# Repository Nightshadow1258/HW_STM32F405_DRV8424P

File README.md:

# STM32F405_DRV8424P
This project contains all files for a Stepper/2xDC-Motor Controller based on a STM32F405 MCU and a DRV8424P GDU.

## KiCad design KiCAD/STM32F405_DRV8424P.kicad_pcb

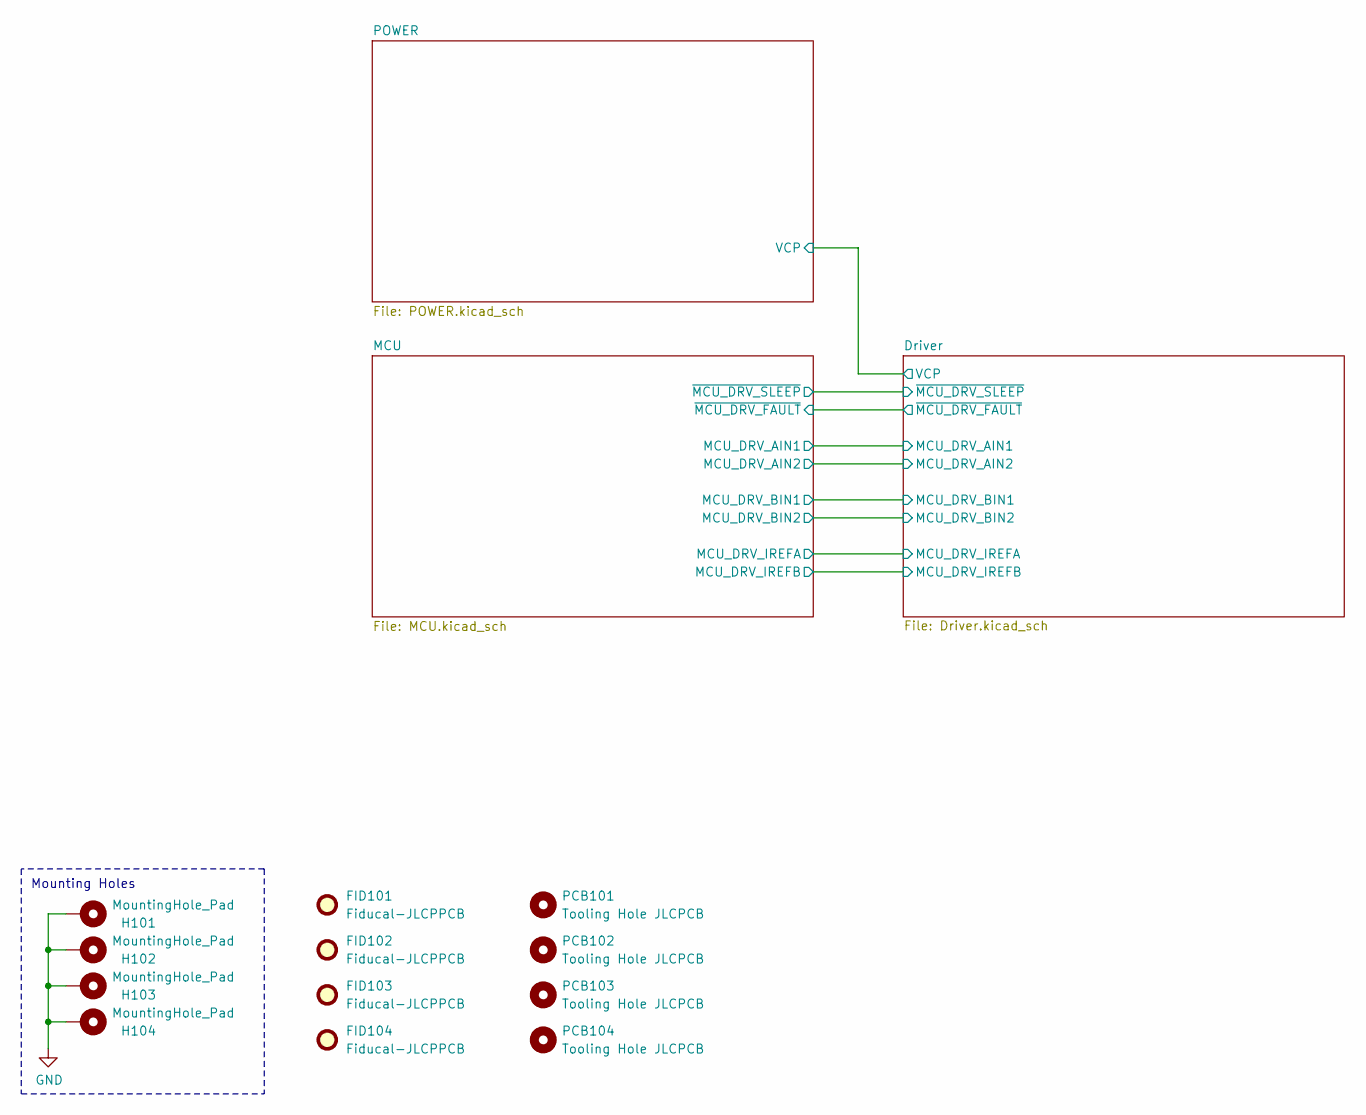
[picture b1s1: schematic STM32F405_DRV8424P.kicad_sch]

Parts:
FID101, FID102, FID103, FID104: Fiducal-JLCPPCB; PCB-FID-JLCPCB
H101, H102, H103, H104: MountingHole_Pad; MountingHole_4.3mm_M4_Pad_Via
PCB101, PCB102, PCB103, PCB104: Tooling Hole JLCPCB; PCB-NPTH-JLCPCB

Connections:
GND: H101.1, H102.1, H103.1, H104.1; also elsewhere on the board

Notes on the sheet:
Mounting Holes

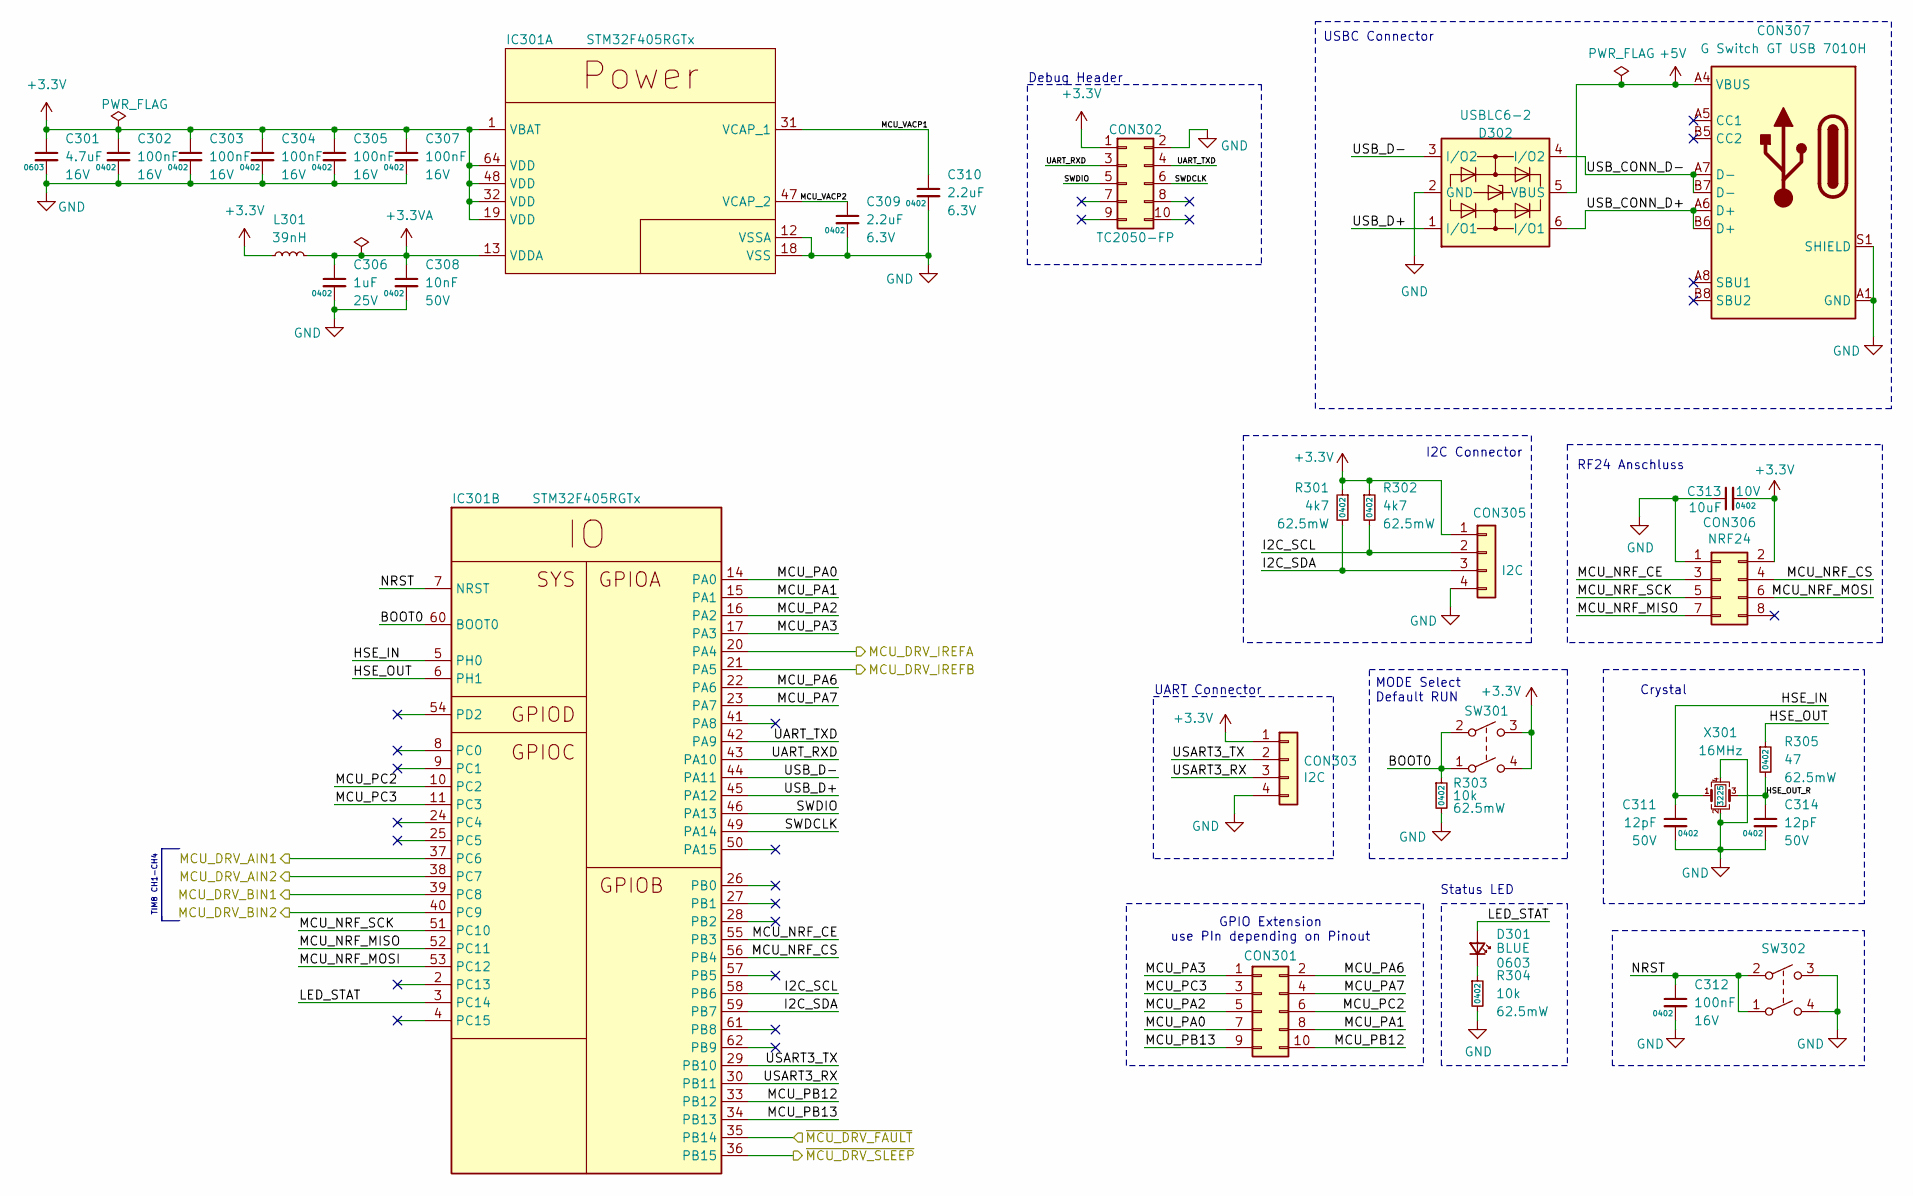
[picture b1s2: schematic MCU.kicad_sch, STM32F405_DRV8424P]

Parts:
C301: 4.7uF; C_0603_1608Metric; Voltage 16V; LCSC Part # C19666
C302, C303, C304, C305, C307, C312: 100nF; C_0402_1005Metric; Voltage 16V; LCSC Part # C1525
C306: 1uF; C_0402_1005Metric; Voltage 25V; LCSC Part # C52923
C308: 10nF; C_0402_1005Metric; Voltage 50V; LCSC Part # C15195
C309, C310: 2.2uF; C_0402_1005Metric; Voltage 6.3V; LCSC Part # C12530
C311, C314: 12pF; C_0402_1005Metric; Voltage 50V; LCSC Part # C1547
C313: 10uF; C_0603_1608Metric; Voltage 10V; LCSC Part # C96446
CON301: GPIO; PinHeader_2x05_P2.54mm_Vertical
CON302: TC2050-FP; CON-TAG-CONNECT_TC2050-IDC
CON303, CON305: I2C; PinHeader_1x04_P2.54mm_Vertical
CON306: NRF24; PinHeader_2x04_P2.54mm_Vertical
CON307: G Switch GT USB 7010H; CON-GEN-USB_C-16P; LCSC Part # C2988369
D301: BLUE; D_0603_1608Metric; LCSC Part # C965807
D302: USBLC6-2; SOT-23-6; LCSC Part # C7519
IC301: STM32F405RGTx; LQFP-64_10x10mm_P0.5mm; LCSC Part # C15742
L301: 39nH; L_0402_1005Metric; LCSC Part # C26443
R301, R302: 4k7; R_0402_1005Metric; Power Rating 62.5mW; LCSC Part # C25900
R303, R304: 10k; R_0402_1005Metric; Power Rating 62.5mW; LCSC Part # C25744
R305: 47; R_0402_1005Metric; Power Rating 62.5mW; LCSC Part # C25118
SW301, SW302: SW-GEN-TS-1187A; SW-PUSH-DPST-XKS-TS-1187A; LCSC Part # C318884
X301: 16MHz; Crystal_SMD_3225-4Pin_3.2x2.5mm; LCSC Part # C12668

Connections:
+3.3V: C301.1, C302.1, C303.1, C304.1, C305.1, C307.1, C313.2, CON302.1, CON303.1, CON305.1, CON306.2, IC301.1 (VBAT), IC301.19 (VDD), IC301.32 (VDD), IC301.48 (VDD), IC301.64 (VDD), L301.1, R301.1, R302.1, SW301.3 (4), SW301.4; also elsewhere on the board
+3.3VA: C306.1, C308.1, IC301.13 (VDDA), L301.2
+5V: CON307.A4 (VBUS), CON307.A9 (VBUS), CON307.B4 (VBUS), CON307.B9 (VBUS), D302.5 (VBUS); also elsewhere on the board
/Driver/MCU_DRV_AIN1: IC301.37 (PC6); also elsewhere on the board
/Driver/MCU_DRV_AIN2: IC301.38 (PC7); also elsewhere on the board
/Driver/MCU_DRV_BIN1: IC301.39 (PC8); also elsewhere on the board
/Driver/MCU_DRV_BIN2: IC301.40 (PC9); also elsewhere on the board
/Driver/MCU_DRV_IREFA: IC301.20 (PA4); also elsewhere on the board
/Driver/MCU_DRV_IREFB: IC301.21 (PA5); also elsewhere on the board
/Driver/~MCU_DRV_FAULT: IC301.35 (PB14); also elsewhere on the board
/Driver/~MCU_DRV_SLEEP: IC301.36 (PB15); also elsewhere on the board
/MCU/BOOT0: IC301.60 (BOOT0), R303.1, SW301.1, SW301.2 (3)
/MCU/HSE_IN: C311.1, IC301.5 (PH0), X301.1
/MCU/HSE_OUT: IC301.6 (PH1), R305.1
/MCU/HSE_OUT_R: C314.1, R305.2, X301.3
/MCU/I2C_SCL: CON305.2, IC301.58 (PB6), R302.2
/MCU/I2C_SDA: CON305.3, IC301.59 (PB7), R301.2
/MCU/LED_STAT: D301.2 (A), IC301.3 (PC14)
/MCU/MCU_NRF_CE: CON306.3, IC301.55 (PB3)
/MCU/MCU_NRF_CS: CON306.4, IC301.56 (PB4)
/MCU/MCU_NRF_MISO: CON306.7, IC301.52 (PC11)
/MCU/MCU_NRF_MOSI: CON306.6, IC301.53 (PC12)
/MCU/MCU_NRF_SCK: CON306.5, IC301.51 (PC10)
/MCU/MCU_PA0: CON301.7, IC301.14 (PA0)
/MCU/MCU_PA1: CON301.8, IC301.15 (PA1)
/MCU/MCU_PA2: CON301.5, IC301.16 (PA2)
/MCU/MCU_PA3: CON301.1, IC301.17 (PA3)
/MCU/MCU_PA6: CON301.2, IC301.22 (PA6)
/MCU/MCU_PA7: CON301.4, IC301.23 (PA7)
/MCU/MCU_PB12: CON301.10, IC301.33 (PB12)
/MCU/MCU_PB13: CON301.9, IC301.34 (PB13)
/MCU/MCU_PC2: CON301.6, IC301.10 (PC2)
/MCU/MCU_PC3: CON301.3, IC301.11 (PC3)
/MCU/MCU_VACP1: C310.1, IC301.31 (VCAP_1)
/MCU/MCU_VACP2: C309.1, IC301.47 (VCAP_2)
/MCU/NRST: C312.1, IC301.7 (NRST), SW302.1, SW302.2 (3)
/MCU/SWDCLK: CON302.6, IC301.49 (PA14)
/MCU/SWDIO: CON302.5, IC301.46 (PA13)
/MCU/UART_RXD: CON302.3, IC301.43 (PA10)
/MCU/UART_TXD: CON302.4, IC301.42 (PA9)
/MCU/USART3_RX: CON303.3, IC301.30 (PB11)
/MCU/USART3_TX: CON303.2, IC301.29 (PB10)
/MCU/USB_CONN_D+: CON307.A6 (D+), CON307.B6 (D+), D302.6 (I/O1)
/MCU/USB_CONN_D-: CON307.A7 (D-), CON307.B7 (D-), D302.4 (I/O2)
/MCU/USB_D+: D302.1 (I/O1), IC301.45 (PA12)
/MCU/USB_D-: D302.3 (I/O2), IC301.44 (PA11)
GND: C301.2, C302.2, C303.2, C304.2, C305.2, C306.2, C307.2, C308.2, C309.2, C310.2, C311.2, C312.2, C313.1, C314.2, CON302.2, CON303.4, CON305.4, CON306.1, CON307.A1 (GND), CON307.A12 (GND), CON307.B1 (GND), CON307.B12 (GND), CON307.S1 (SHIELD), D302.2 (GND), IC301.12 (VSSA), IC301.18 (VSS), IC301.63 (VSS), R303.2, R304.2, SW302.3 (4), SW302.4, X301.2, X301.4; also elsewhere on the board
unnamed: D301.1 (K), R304.1

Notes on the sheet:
Debug Header
GPIO Extension use PIn depending on Pinout
MODE Select Default RUN
Status LED
TIM8 CH1-CH4
UART Connector
Crystal
I2C Connector
USBC Connector
RF24 Anschluss

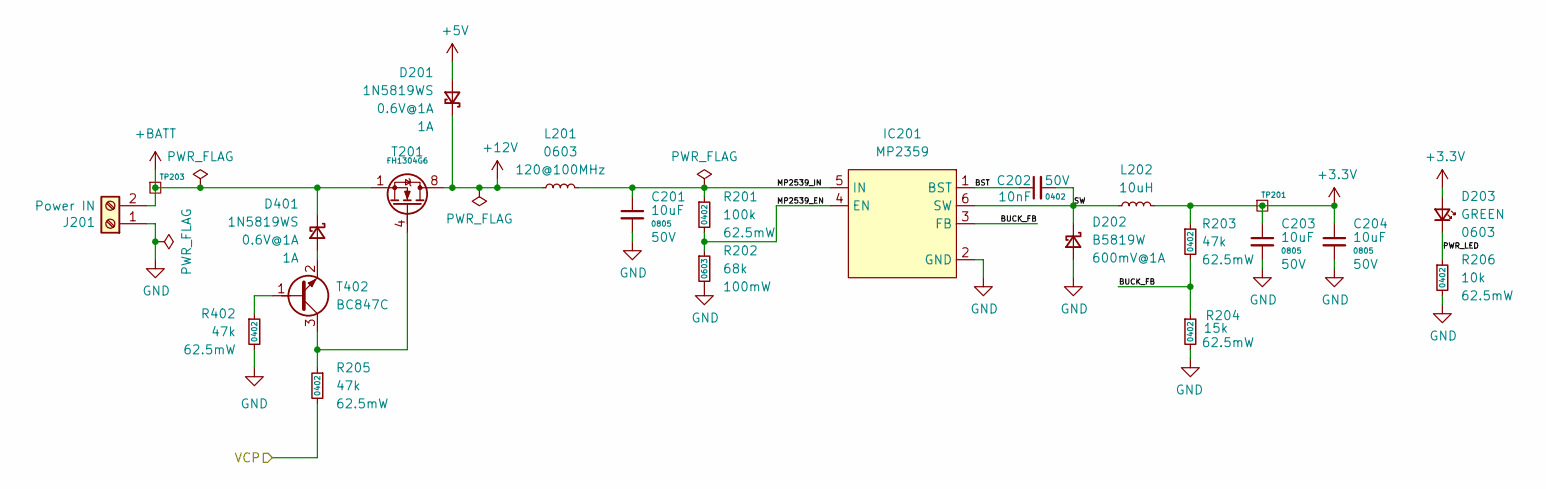
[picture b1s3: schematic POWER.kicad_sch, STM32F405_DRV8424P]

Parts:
C201, C203, C204: 10uF; C_0805_2012Metric; Voltage 50V; LCSC Part # C440198
C202: 10nF; C_0402_1005Metric; Voltage 50V; LCSC Part # C15195
D201, D401: 1N5819WS; D_SOD-323; LCSC Part # C191023
D202: B5819W; D_SOD-123; LCSC Part # C8598
D203: GREEN; D_0603_1608Metric; LCSC Part # C965804
IC201: MP2359; SOT-23-6; LCSC Part # C2959845
J201: Power IN; TerminalBlock_MetzConnect_Type101_RT01602HBWC_1x02_P5.08mm_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
L201: FB-BLM18PG121SN1; L_0603_1608Metric; LCSC Part # C14709
L202: 10uH; L_SXN_SMNR4020; LCSC Part # C135263
R201: 100k; R_0402_1005Metric; Power Rating 62.5mW; LCSC Part # C25741
R202: 68k; C_0603_1608Metric; Power Rating 100mW; LCSC Part # C23231
R203, R205, R402: 47k; R_0402_1005Metric; Power Rating 62.5mW; LCSC Part # C25792
R204: 15k; R_0402_1005Metric; Power Rating 62.5mW; LCSC Part # C25756
R206: 10k; R_0402_1005Metric; Power Rating 62.5mW; LCSC Part # C25744
T201: FH1304G6; DFN-8-1EP_3x3mm_P0.65mm_EP1.6x2.56mm_ThermalVias; LCSC Part # C5159042
T402: BC847C; SOT-23; LCSC Part # C8664
TP201, TP203: Testpoint-BASE; TP_THT_D0.8mm

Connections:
+3.3V: C203.1, C204.1, D203.2 (A), L202.2, R203.1, TP201.1; also elsewhere on the board
+5V: D201.2 (A); also elsewhere on the board
+12V: D201.1 (K), L201.1, T201.5 (D), T201.6 (D), T201.7 (D), T201.8 (D), T201.9 (D); also elsewhere on the board
+BATT: D401.1 (K), J201.2, T201.1 (S), T201.2 (S), T201.3 (S), TP203.1
/Driver/VCP: R205.2; also elsewhere on the board
/POWER/BST: C202.1, IC201.1 (BST)
/POWER/BUCK_FB: IC201.3 (FB), R203.2, R204.1
/POWER/MP2539_EN: IC201.4 (EN), R201.2, R202.1
/POWER/MP2539_IN: C201.1, IC201.5 (IN), L201.2, R201.1
/POWER/PWR_LED: D203.1 (K), R206.1
/POWER/SW: C202.2, D202.1 (K), IC201.6 (SW), L202.1
GND: C201.2, C203.2, C204.2, D202.2 (A), IC201.2 (GND), J201.1, R202.2, R204.2, R206.2, R402.2; also elsewhere on the board
unnamed: D401.2 (A), T402.2 (E)
unnamed: R205.1, T201.4 (G), T402.3 (C)
unnamed: R402.1, T402.1 (B)

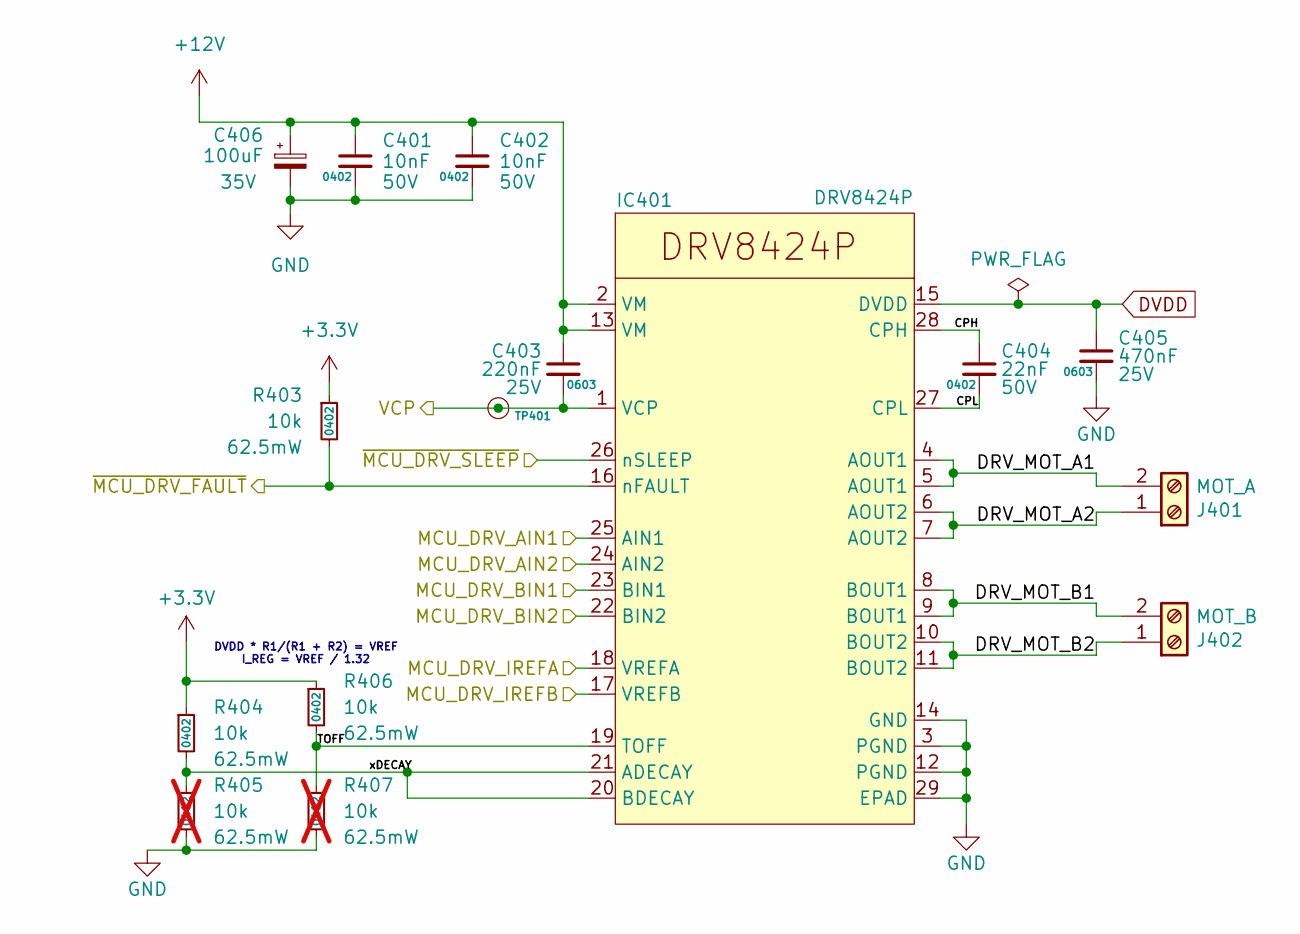
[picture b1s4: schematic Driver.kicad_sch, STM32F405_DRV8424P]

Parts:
C401, C402: 10nF; C_0402_1005Metric; Voltage 50V; LCSC Part # C15195
C403: 220nF; C_0603_1608Metric; Voltage 25V; LCSC Part # C21120
C404: 22nF; C_0402_1005Metric; Voltage 50V; LCSC Part # C1532
C405: 470nF; C_0603_1608Metric; Voltage 25V; LCSC Part # C1623
C406: 100uF; CP_Elec_6.3x7.7; LCSC Part # C72478
IC401: DRV8424P; HTSSOP-28-1EP_4.4x9.7mm_P0.65mm_EP3.4x9.5mm_ThermalVias; LCSC Part # C2864825
J401: MOT_A; TerminalBlock_MetzConnect_Type101_RT01602HBWC_1x02_P5.08mm_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
J402: MOT_B; TerminalBlock_MetzConnect_Type101_RT01602HBWC_1x02_P5.08mm_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
R403, R404, R406: 10k; R_0402_1005Metric; Power Rating 62.5mW; LCSC Part # C25744
R405, R407: 10k; R_0402_1005Metric; Power Rating 62.5mW; LCSC Part # C25744; not fitted
TP401: TP; TP_Pad_D0.9mm

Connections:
+3.3V: R403.1, R404.1, R406.1; also elsewhere on the board
+12V: C401.1, C402.1, C403.1, C406.1, IC401.2 (VM), IC401.13 (VM); also elsewhere on the board
/Driver/CPH: C404.1, IC401.28 (CPH)
/Driver/CPL: C404.2, IC401.27 (CPL)
/Driver/DRV_MOT_A1: IC401.4 (AOUT1), IC401.5 (AOUT1), J401.2
/Driver/DRV_MOT_A2: IC401.6 (AOUT2), IC401.7 (AOUT2), J401.1
/Driver/DRV_MOT_B1: IC401.8 (BOUT1), IC401.9 (BOUT1), J402.2
/Driver/DRV_MOT_B2: IC401.10 (BOUT2), IC401.11 (BOUT2), J402.1
/Driver/MCU_DRV_AIN1: IC401.25 (AIN1); also elsewhere on the board
/Driver/MCU_DRV_AIN2: IC401.24 (AIN2); also elsewhere on the board
/Driver/MCU_DRV_BIN1: IC401.23 (BIN1); also elsewhere on the board
/Driver/MCU_DRV_BIN2: IC401.22 (BIN2); also elsewhere on the board
/Driver/MCU_DRV_IREFA: IC401.18 (VREFA); also elsewhere on the board
/Driver/MCU_DRV_IREFB: IC401.17 (VREFB); also elsewhere on the board
/Driver/TOFF: IC401.19 (TOFF), R406.2, R407.1
/Driver/VCP: C403.2, IC401.1 (VCP), TP401.1; also elsewhere on the board
/Driver/xDECAY: IC401.20 (BDECAY), IC401.21 (ADECAY), R404.2, R405.1
/Driver/~MCU_DRV_FAULT: IC401.16 (nFAULT), R403.2; also elsewhere on the board
/Driver/~MCU_DRV_SLEEP: IC401.26 (nSLEEP); also elsewhere on the board
DVDD: C405.1, IC401.15 (DVDD)
GND: C401.2, C402.2, C405.2, C406.2, IC401.3 (PGND), IC401.12 (PGND), IC401.14 (GND), IC401.29 (EPAD), R405.2, R407.2; also elsewhere on the board

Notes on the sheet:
DVDD * R1/(R1 + R2) = VREF I_REG = VREF / 1.32

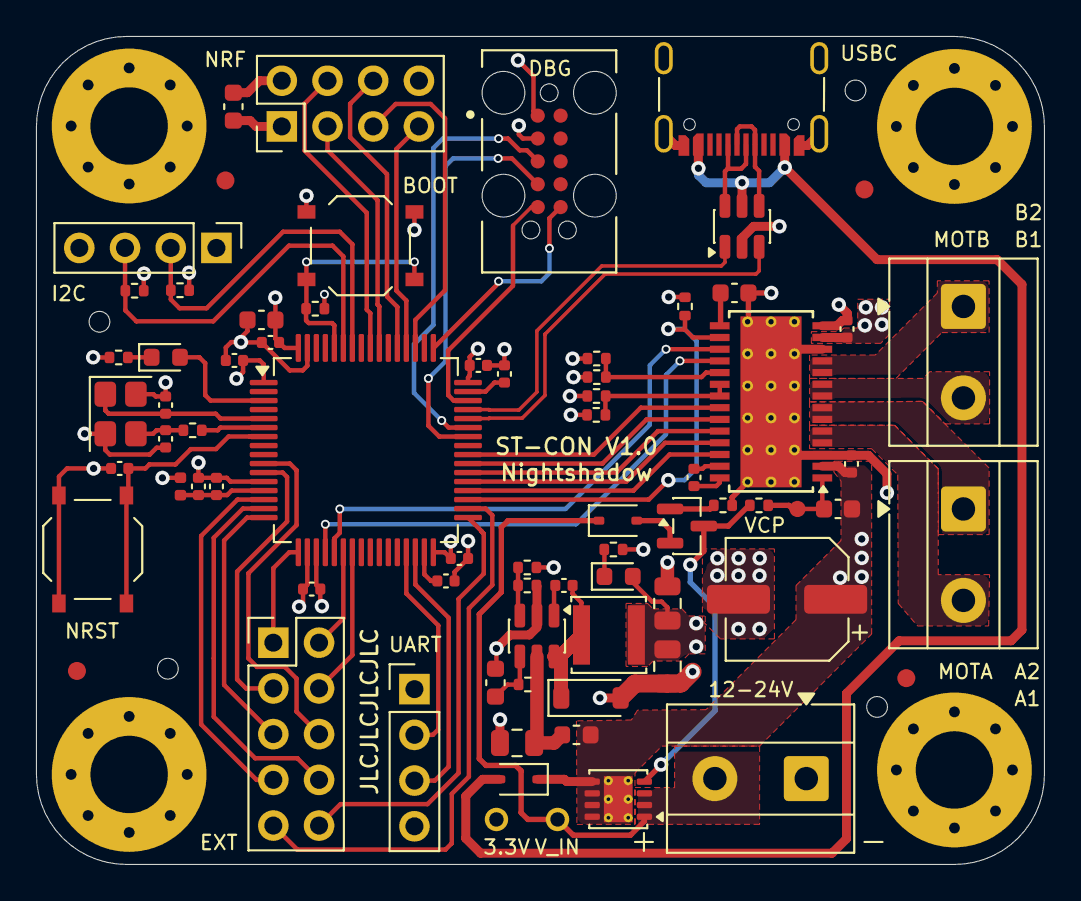
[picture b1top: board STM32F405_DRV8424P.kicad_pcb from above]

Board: 4 copper layers, 56.0 x 46.0 mm, 82 parts (0 on the bottom side), 69 nets.

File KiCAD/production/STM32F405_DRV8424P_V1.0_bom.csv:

Designator,Footprint,Quantity,Value,LCSC Part #
"C201, C203, C204",0805,3,10uF,C440198
"C202, C308, C401, C402",0402,4,10nF,C15195
C301,0603,1,4.7uF,C19666
"C302, C303, C304, C305, C307, C312",0402,6,100nF,C1525
C306,0402,1,1uF,C52923
"C309, C310",0402,2,2.2uF,C12530
"C311, C314",0402,2,12pF,C1547
C313,0603,1,10uF,C96446
C403,0603,1,220nF,C21120
C404,0402,1,22nF,C1532
C405,0603,1,470nF,C1623
C406,CP_Elec_6.3x7.7,1,100uF,C72478
CON301,PinHeader_2x05_P2.54mm_Vertical,1,GPIO,
CON302,CON-TAG-CONNECT_TC2050-IDC,1,TC2050-FP,
"CON303, CON305",PinHeader_1x04_P2.54mm_Vertical,2,I2C,
CON306,PinHeader_2x04_P2.54mm_Vertical,1,NRF24,
CON307,CON-GEN-USB_C-16P,1,G Switch GT USB 7010H,C2988369
"D201, D401",D_SOD-323,2,1N5819WS,C191023
D202,D_SOD-123,1,B5819W,C8598
D203,0603,1,GREEN,C965804
D301,0603,1,BLUE,C965807
D302,SOT-23-6,1,USBLC6-2,C7519
IC201,SOT-23-6,1,MP2359,C2959845
IC301,LQFP-64_10x10mm_P0.5mm,1,STM32F405RGTx,C15742
IC401,HTSSOP-28-1EP_4.4x9.7mm_P0.65mm_EP3.4x9.5mm_ThermalVias,1,DRV8424P,C2864825
J201,TerminalBlock_MetzConnect_Type101_RT01602HBWC_1x02_P5.08mm_Horizontal,1,Power IN,
J401,TerminalBlock_MetzConnect_Type101_RT01602HBWC_1x02_P5.08mm_Horizontal,1,MOT_A,
J402,TerminalBlock_MetzConnect_Type101_RT01602HBWC_1x02_P5.08mm_Horizontal,1,MOT_B,
L201,0603,1,FB-BLM18PG121SN1,C14709
L202,L_SXN_SMNR4020,1,10uH,    C135263
L301,0402,1,39nH,C26443
R201,0402,1,100k,C25741
R202,0603,1,68k,C23231
"R203, R205, R402",0402,3,47k,C25792
R204,0402,1,15k,C25756
"R206, R303, R304, R403, R404, R406",0402,6,10k,C25744
"R301, R302",0402,2,4k7,C25900
R305,0402,1,47,C25118
"SW301, SW302",SW-PUSH-DPST-XKS-TS-1187A,2,SW-GEN-TS-1187A,C318884
T201,DFN-8-1EP_3x3mm_P0.65mm_EP1.6x2.56mm_ThermalVias,1,FH1304G6,C5159042
T402,SOT-23,1,BC847C,C8664
X301,Crystal_SMD_3225-4Pin_3.2x2.5mm,1,16MHz,C12668

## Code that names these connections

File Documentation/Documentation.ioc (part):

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Mcu.Name=STM32F405RGTx
Mcu.Package=LQFP64
Mcu.UserName=STM32F405RGTx
PA10.Mode=Asynchronous
PA10.Signal=USART1_RX
PA11.Mode=Device_Only
PA11.Signal=USB_OTG_FS_DM
PA12.Mode=Device_Only
PA12.Signal=USB_OTG_FS_DP
PA13.Mode=Serial_Wire
PA13.Signal=SYS_JTMS-SWDIO
PA14.Mode=Serial_Wire
PA14.Signal=SYS_JTCK-SWCLK
PA15.Mode=NSS_Signal_Hard_Output
PA15.Signal=SPI3_NSS
PA4.Signal=COMP_DAC1_group
PA5.Signal=COMP_DAC2_group
PA9.Mode=Asynchronous
PA9.Signal=USART1_TX
PB10.Mode=Asynchronous
PB10.Signal=USART3_TX
PB11.Mode=Asynchronous
PB11.Signal=USART3_RX
PB12.Mode=NSS_Signal_Hard_Output
PB12.Signal=SPI2_NSS
PB13.Mode=Full_Duplex_Master
PB13.Signal=SPI2_SCK
PB6.Mode=I2C
PB6.Signal=I2C1_SCL
PB7.Mode=I2C
PB7.Signal=I2C1_SDA
PC10.Mode=Full_Duplex_Master
PC10.Signal=SPI3_SCK
PC11.Mode=Full_Duplex_Master
PC11.Signal=SPI3_MISO
PC12.Mode=Full_Duplex_Master
PC12.Signal=SPI3_MOSI
PC2.Mode=Full_Duplex_Master
PC2.Signal=SPI2_MISO
PC3.Mode=Full_Duplex_Master
PC3.Signal=SPI2_MOSI
PC6.Signal=S_TIM8_CH1
PC7.Signal=S_TIM8_CH2
PC8.Signal=S_TIM8_CH3
PC9.Signal=S_TIM8_CH4
PH0-OSC_IN.Mode=HSE-External-Oscillator
PH0-OSC_IN.Signal=RCC_OSC_IN
PH1-OSC_OUT.Mode=HSE-External-Oscillator
PH1-OSC_OUT.Signal=RCC_OSC_OUT
RCC.HSE_VALUE=16000000
RCC.SYSCLKFreq_VALUE=168000000
RCC.SYSCLKSource=RCC_SYSCLKSOURCE_PLLCLK
board=custom

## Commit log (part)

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2026-02-22 Production Ready V1.0
